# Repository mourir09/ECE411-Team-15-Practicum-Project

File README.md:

# ECE411-Team-15-Practicum-Project
Practicum Project

hello

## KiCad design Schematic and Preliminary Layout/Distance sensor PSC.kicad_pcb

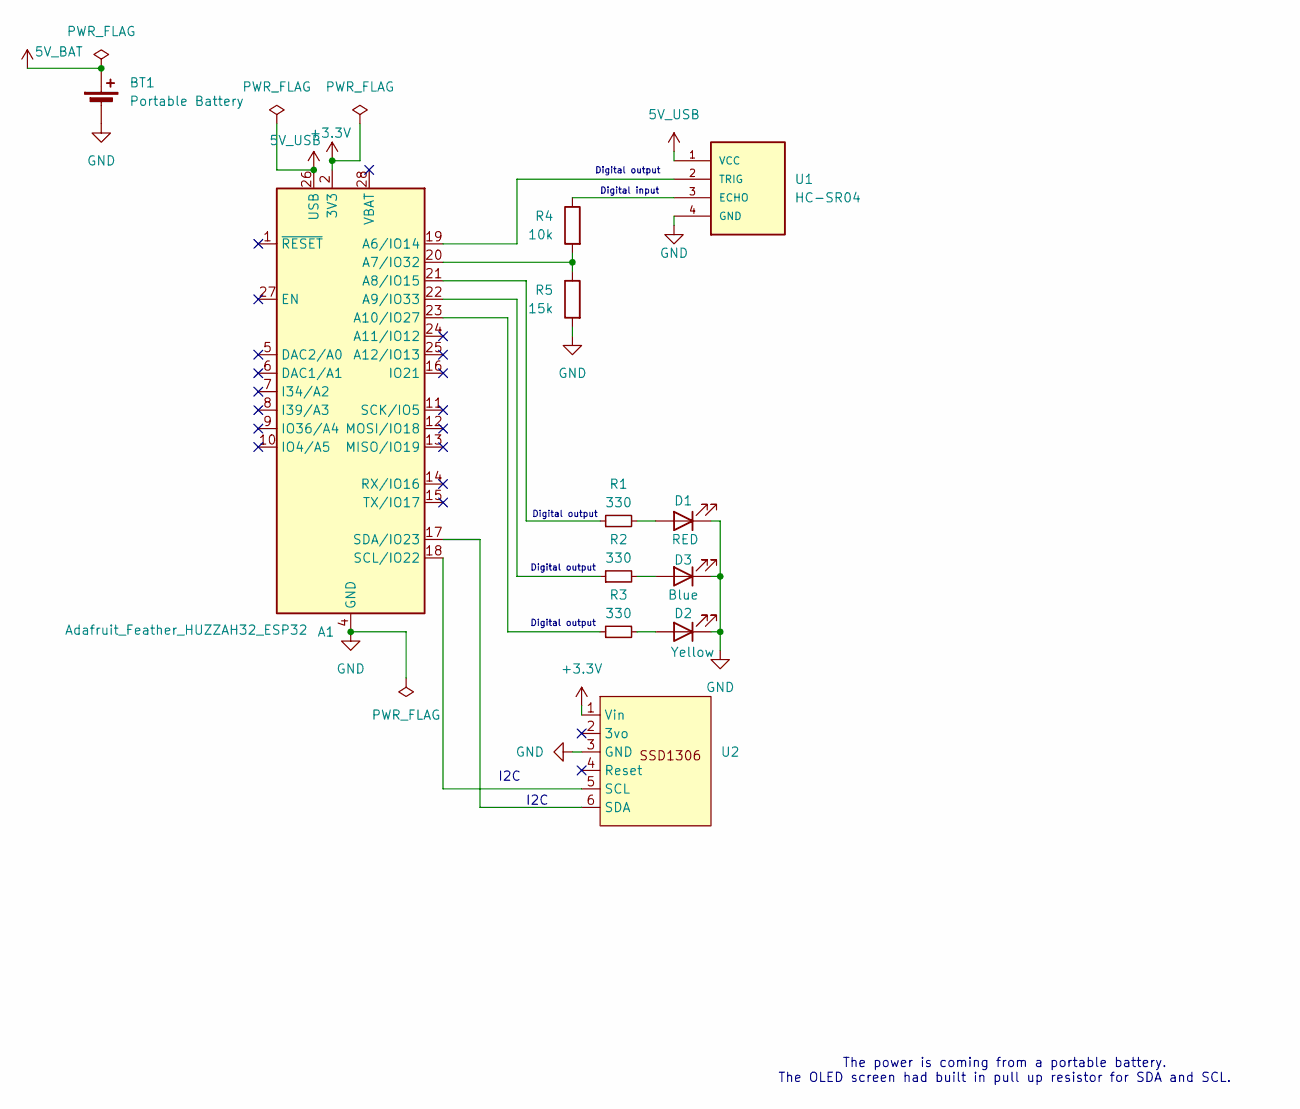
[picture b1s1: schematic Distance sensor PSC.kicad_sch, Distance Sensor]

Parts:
A1: Adafruit_Feather_HUZZAH32_ESP32; Adafruit_Feather
BT1: Portable Battery
D1: RED; LED_D5.0mm
D2: Yellow; LED_D5.0mm
D3: Blue; LED_D5.0mm
R1, R2, R3: 330; R_Axial_DIN0207_L6.3mm_D2.5mm_P7.62mm_Horizontal
R4: 10k; R_Axial_DIN0207_L6.3mm_D2.5mm_P7.62mm_Horizontal
R5: 15k; R_Axial_DIN0207_L6.3mm_D2.5mm_P7.62mm_Horizontal
U1: HC-SR04; PinHeader_1x04_P2.54mm_Vertical
U2: Adafruit_SSD1306

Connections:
+3.3V: A1.2 (3V3), U2.1 (Vin)
+5V: A1.26 (USB), U1.1 (VCC)
GND: A1.4 (GND), BT1.2 (-), D1.1 (K), D2.1 (K), D3.1 (K), R5.2, U1.4 (GND), U2.3 (GND)
unnamed: A1.19 (A6/IO14), U1.2 (TRIG)
unnamed: A1.20 (A7/IO32), R4.2, R5.1
unnamed: A1.21 (A8/IO15), R1.1
unnamed: A1.22 (A9/IO33), R2.1
unnamed: A1.23 (A10/IO27), R3.1
unnamed: A1.18 (SCL/IO22), U2.5 (SCL)
unnamed: A1.17 (SDA/IO23), U2.6 (SDA)
unnamed: D1.2 (A), R1.2
unnamed: D2.2 (A), R3.2
unnamed: D3.2 (A), R2.2
unnamed: R4.1, U1.3 (ECHO)

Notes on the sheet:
Digital output
The power is coming from a portable battery. The OLED screen had built in pull up resistor for SDA and SCL.
I2C
Digital input

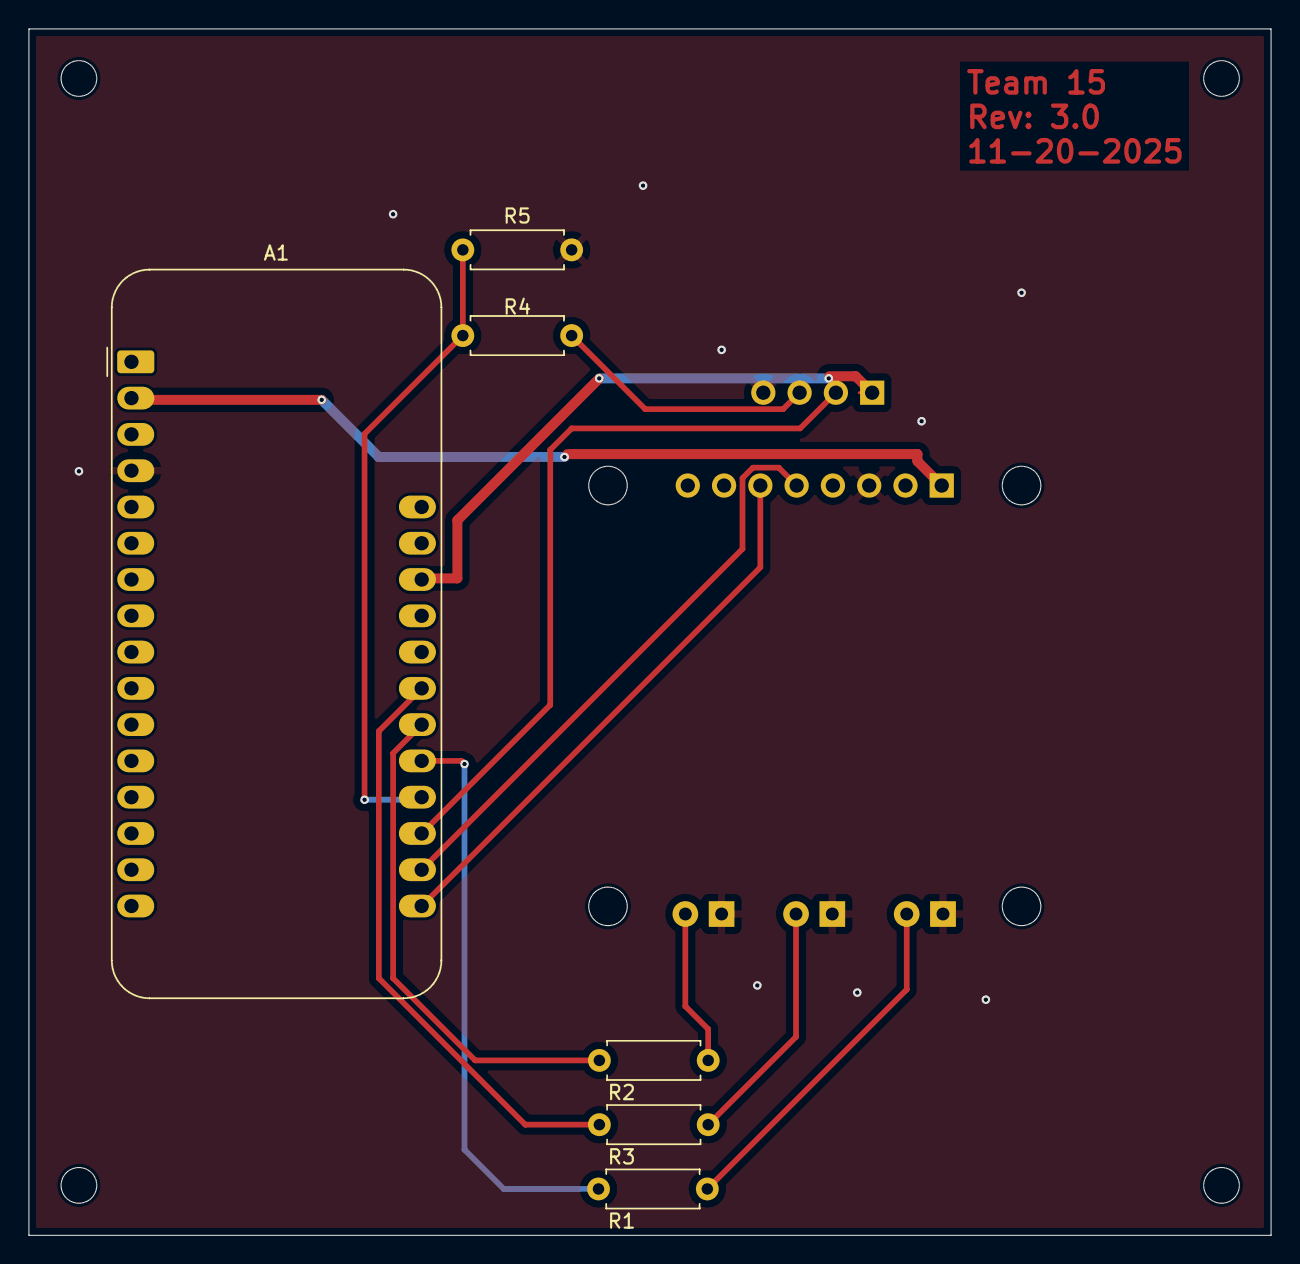
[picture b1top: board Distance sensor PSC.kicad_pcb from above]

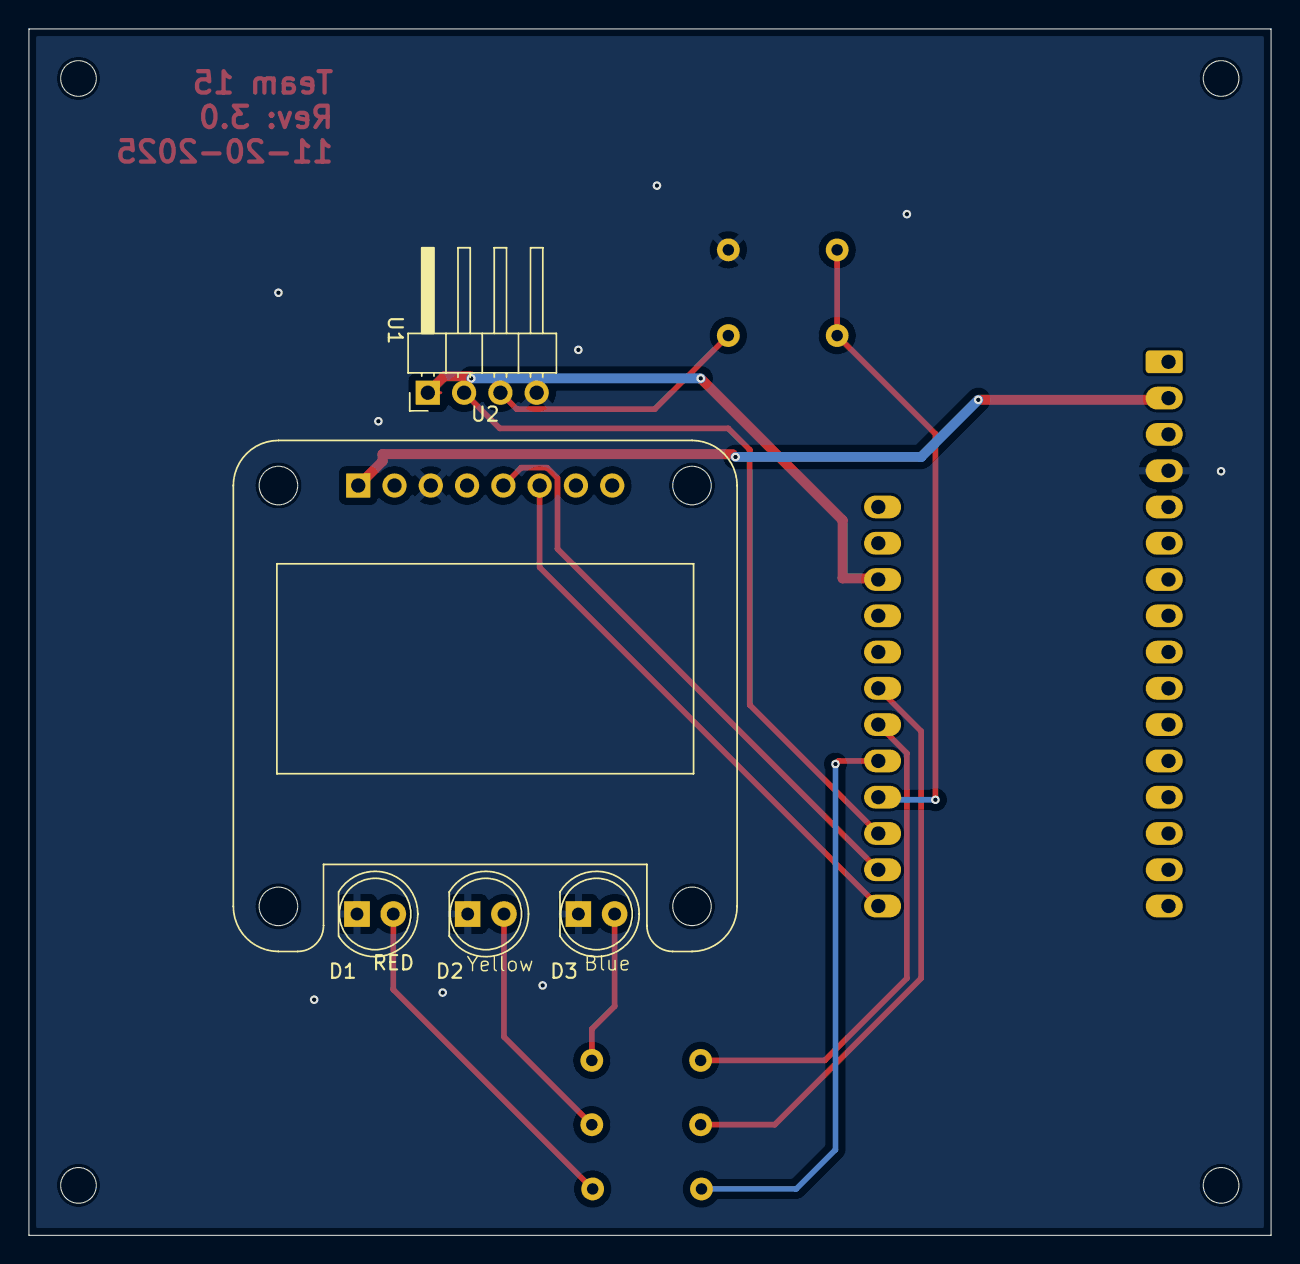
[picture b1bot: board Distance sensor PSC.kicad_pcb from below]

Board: 2 copper layers, 87.0 x 84.5 mm, 11 parts (5 on the bottom side), 14 nets.

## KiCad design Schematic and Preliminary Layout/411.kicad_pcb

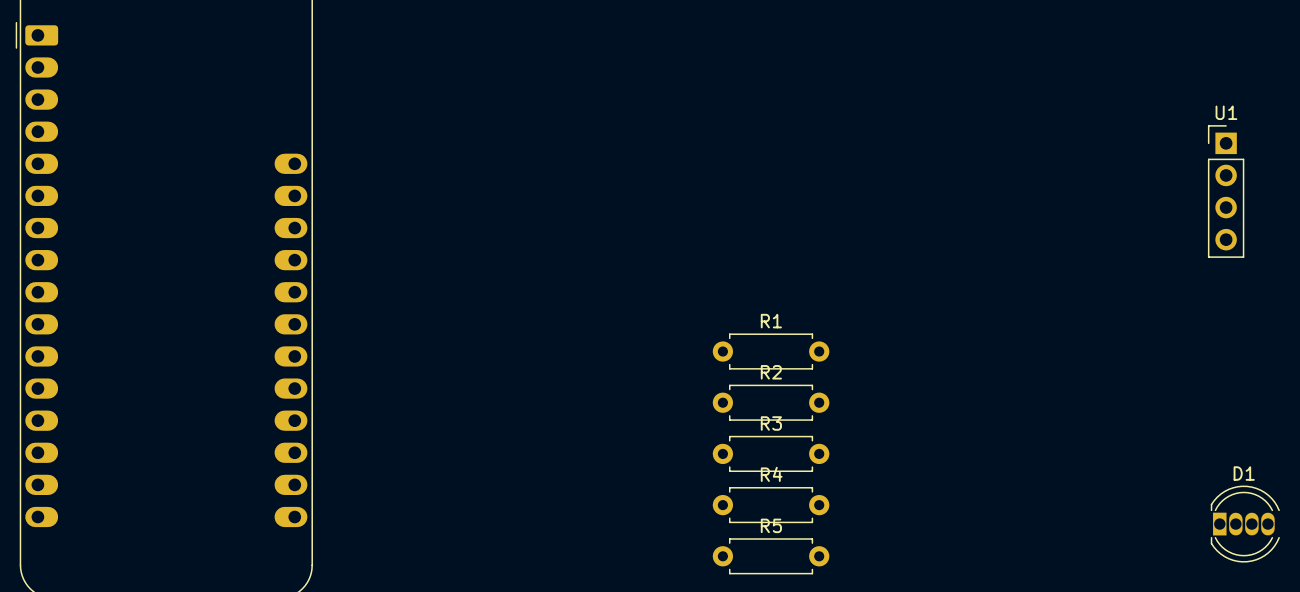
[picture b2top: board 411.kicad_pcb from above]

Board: 2 copper layers, 8 parts (0 on the bottom side), 11 nets, no tracks yet.

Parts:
A1: Adafruit_Feather_HUZZAH32_ESP32; Adafruit_Feather
D1: LED_ARGB; LED_D5.0mm-4_RGB
R1, R2, R3: 330; R_Axial_DIN0207_L6.3mm_D2.5mm_P7.62mm_Horizontal
R4: 10k; R_Axial_DIN0207_L6.3mm_D2.5mm_P7.62mm_Horizontal
R5: 15k; R_Axial_DIN0207_L6.3mm_D2.5mm_P7.62mm_Horizontal
U1: HC-SR04; PinHeader_1x04_P2.54mm_Vertical

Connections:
GND: D1.1 (A), R5.2, U1.4 (GND)
unnamed: A1.20 (A7/IO32), R1.1
unnamed: A1.24 (A11/IO12), R2.1
unnamed: A1.25 (A12/IO13), R3.1
unnamed: A1.11 (SCK/IO5), U1.2 (TRIG)
unnamed: A1.17 (SDA/IO23), R4.2, R5.1
unnamed: A1.26 (USB), U1.1 (VCC)
unnamed: D1.4 (BK), R3.2
unnamed: D1.3 (GK), R2.2
unnamed: D1.2 (RK), R1.2
unnamed: R4.1, U1.3 (ECHO)

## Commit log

2025-10-16 Initial commit: add README
2025-10-30 Add ESP32 Wiring Diagram
2025-11-13 Schedule
2025-11-13 removed duplicate
2025-11-13 Moving files to folders
2025-11-13 Moved files to folders
2025-11-13 Add files
2025-11-13 Moved files
2025-11-13 Change folder names
2025-11-20 Added schematic and pcb
2025-11-20 Readded schematic and pcb layout
2025-11-20 Updated PCB
2025-11-20 Updated Schematic
2025-11-20 added team version and date to PCB
2025-11-22 Updated BOM
2025-12-03 Added test plans
2025-12-12 Re-added Schedule
2025-12-12 Updated test plan
2025-12-12 Added code
